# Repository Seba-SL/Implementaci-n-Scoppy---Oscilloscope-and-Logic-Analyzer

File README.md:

<h1>  Implementación Scoppy - Oscilloscope and Logic Analyzer </h1>

Fuente: https://oscilloscope.fhdm.xyz/

En este repositorio se implementa el diseño N° 5 de el proyecho Scoppy para Raspberry Pico W de microcontrolador RP2040.

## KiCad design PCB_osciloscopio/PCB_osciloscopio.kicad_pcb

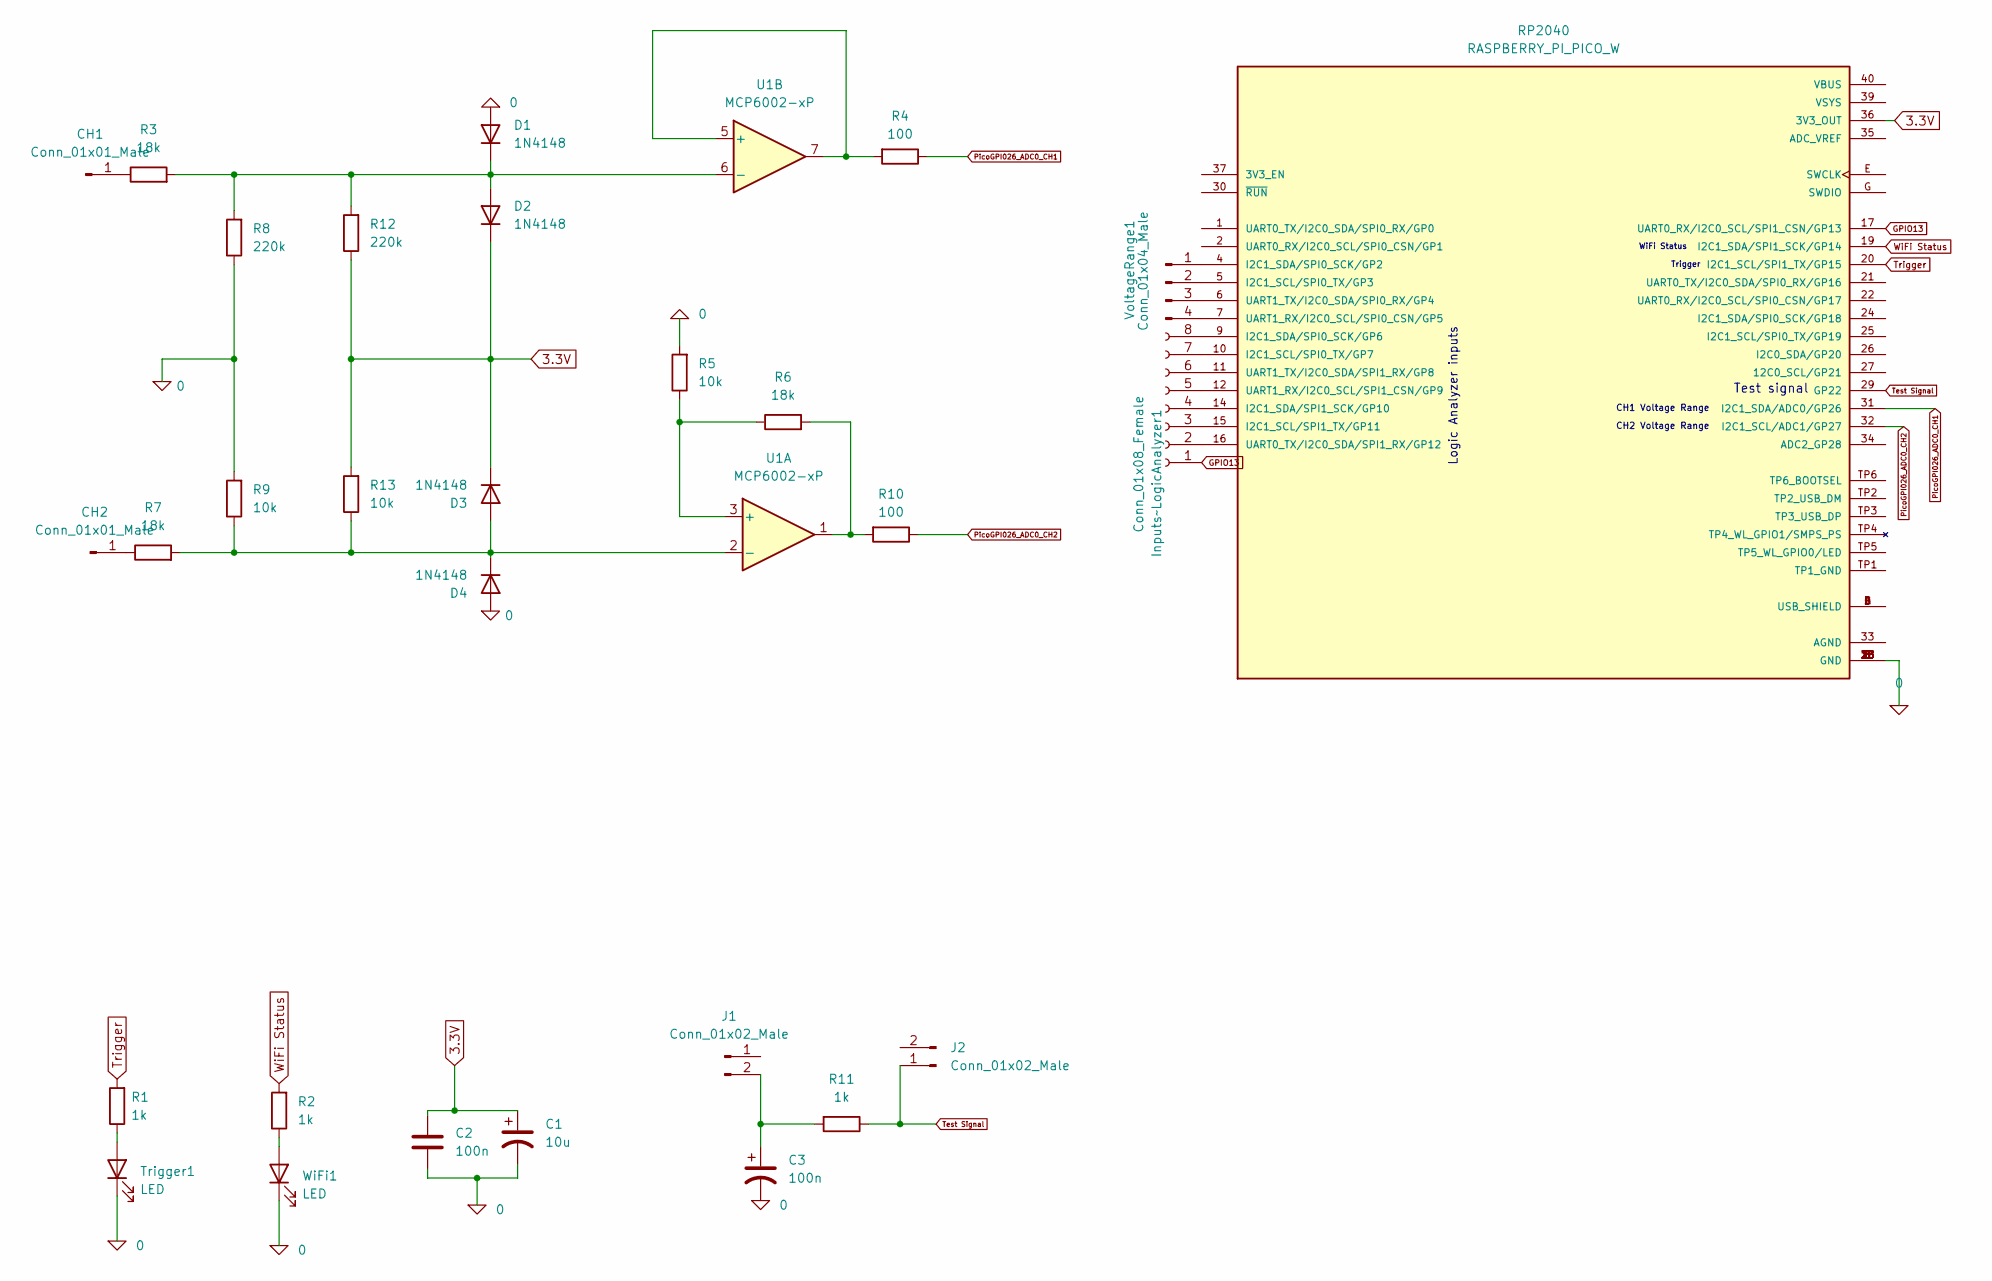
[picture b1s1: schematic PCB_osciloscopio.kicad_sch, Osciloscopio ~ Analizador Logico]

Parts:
C1: 10u; CP_Radial_D4.0mm_P1.50mm
C2: 100n; CP_Radial_D4.0mm_P1.50mm
C3: 100n; CP_Radial_D4.0mm_P2.00mm
CH1, CH2: Conn_01x01_Male; PinHeader_1x01_P1.00mm_Vertical
D1, D2, D3, D4: 1N4148; D_DO-35_SOD27_P7.62mm_Horizontal
Inputs~LogicAnalyzer1: Conn_01x08_Female; PinSocket_1x08_P2.54mm_Vertical
J1, J2: Conn_01x02_Male; PinHeader_1x02_P2.00mm_Vertical
R1, R2, R11: 1k; R_Axial_DIN0204_L3.6mm_D1.6mm_P7.62mm_Horizontal
R3, R6, R7: 18k; R_Axial_DIN0204_L3.6mm_D1.6mm_P7.62mm_Horizontal
R4, R10: 100; R_Axial_DIN0204_L3.6mm_D1.6mm_P7.62mm_Horizontal
R5, R9, R13: 10k; R_Axial_DIN0204_L3.6mm_D1.6mm_P7.62mm_Horizontal
R8, R12: 220k; R_Axial_DIN0204_L3.6mm_D1.6mm_P7.62mm_Horizontal
RP2040: RASPBERRY_PI_PICO_W; MODULE_RASPBERRY_PI_PICO_W; PARTREV 2.4
Trigger1: LED; LED_D3.0mm
U1: MCP6002-xP; DIP-8_W10.16mm_LongPads
VoltageRange1: Conn_01x04_Male; PinHeader_1x04_P2.00mm_Vertical
WiFi1: LED; LED_D3.0mm

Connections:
0: C1.2, C2.2, C3.2, D1.2 (A), D4.2 (A), R5.2, R8.1, R9.2, RP2040.3 (GND), RP2040.8 (GND), RP2040.13 (GND), RP2040.18 (GND), RP2040.23 (GND), RP2040.28 (GND), RP2040.38 (GND), RP2040.F (GND), Trigger1.1 (K), WiFi1.1 (K)
3.3V: C1.1, C2.1, D2.1 (K), D3.1 (K), R12.1, R13.2, RP2040.36 (3V3_OUT)
GPIO13: Inputs~LogicAnalyzer1.1, RP2040.17 (UART0_RX/I2C0_SCL/SPI1_CSN/GP13)
unnamed: C3.1, J1.2, R11.2
unnamed: CH1.1, R3.1
unnamed: CH2.1, R7.1
unnamed: D1.1 (K), D2.2 (A), R3.2, R8.2, R12.2, U1.6 (-)
unnamed: D3.2 (A), D4.1 (K), R7.2, R9.1, R13.1, U1.2 (-)
unnamed: Inputs~LogicAnalyzer1.2, RP2040.16 (UART0_TX/I2C0_SDA/SPI1_RX/GP12)
unnamed: Inputs~LogicAnalyzer1.3, RP2040.15 (I2C1_SCL/SPI1_TX/GP11)
unnamed: Inputs~LogicAnalyzer1.4, RP2040.14 (I2C1_SDA/SPI1_SCK/GP10)
unnamed: Inputs~LogicAnalyzer1.5, RP2040.12 (UART1_RX/I2C0_SCL/SPI1_CSN/GP9)
unnamed: Inputs~LogicAnalyzer1.6, RP2040.11 (UART1_TX/I2C0_SDA/SPI1_RX/GP8)
unnamed: Inputs~LogicAnalyzer1.7, RP2040.10 (I2C1_SCL/SPI0_TX/GP7)
unnamed: Inputs~LogicAnalyzer1.8, RP2040.9 (I2C1_SDA/SPI0_SCK/GP6)
unnamed: R1.1, Trigger1.2 (A)
unnamed: R2.1, WiFi1.2 (A)
unnamed: R4.2, U1.5 (+), U1.7
unnamed: R5.1, R6.1, U1.3 (+)
unnamed: R6.2, R10.2, U1.1
unnamed: RP2040.4 (I2C1_SDA/SPI0_SCK/GP2), VoltageRange1.1
unnamed: RP2040.5 (I2C1_SCL/SPI0_TX/GP3), VoltageRange1.2
unnamed: RP2040.6 (UART1_TX/I2C0_SDA/SPI0_RX/GP4), VoltageRange1.3
unnamed: RP2040.7 (UART1_RX/I2C0_SCL/SPI0_CSN/GP5), VoltageRange1.4
unnamed: RP2040.A (USB_SHIELD), RP2040.B (USB_SHIELD), RP2040.C (USB_SHIELD), RP2040.D (USB_SHIELD)
PicoGPI026_ADC0_CH1: R4.1, RP2040.31 (I2C1_SDA/ADC0/GP26)
PicoGPI026_ADC0_CH2: R10.1, RP2040.32 (I2C1_SCL/ADC1/GP27)
Test Signal: J2.1, R11.1, RP2040.29 (GP22)
Trigger: R1.2, RP2040.20 (I2C1_SCL/SPI1_TX/GP15)
WiFi Status: R2.2, RP2040.19 (I2C1_SDA/SPI1_SCK/GP14)

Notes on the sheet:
CH1 Voltage Range
CH2 Voltage Range
Test signal
Trigger
Logic Analyzer inputs
WiFi Status

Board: 2 copper layers, 30 parts (0 on the bottom side), 30 nets, no tracks yet.

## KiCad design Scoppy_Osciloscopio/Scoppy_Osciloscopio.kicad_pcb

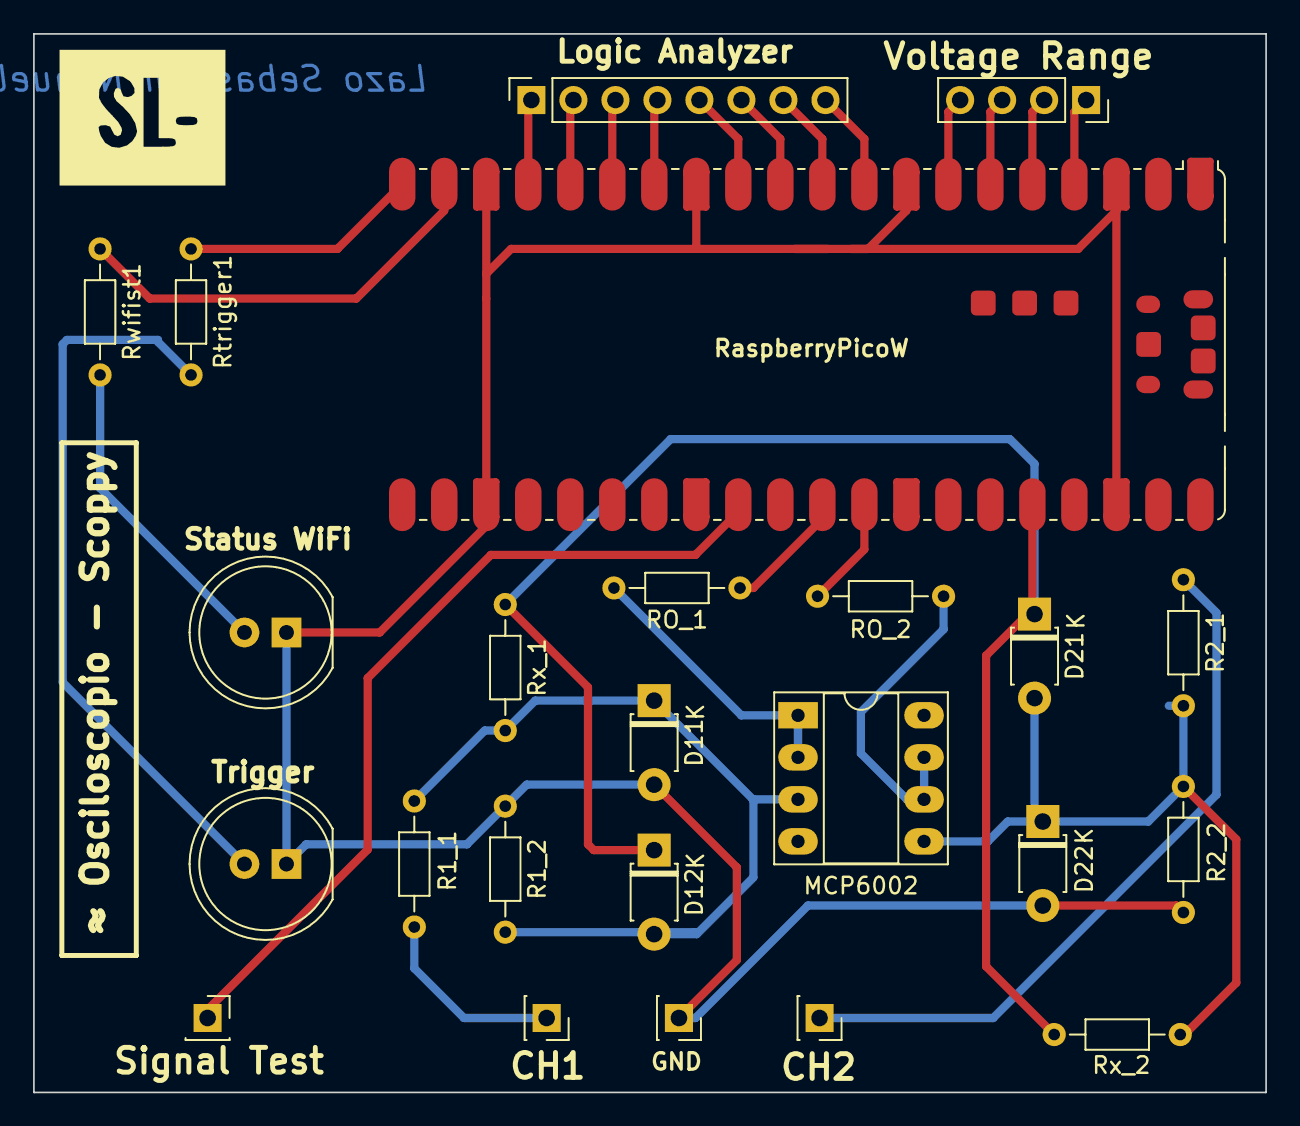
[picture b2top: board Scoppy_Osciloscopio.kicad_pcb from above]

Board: 2 copper layers, 74.5 x 64.0 mm, 24 parts (0 on the bottom side), 27 nets.

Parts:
CH1: CH1_input; PinSocket_1x01_P2.54mm_Vertical
CH2: CH2_input; PinSocket_1x01_P2.54mm_Vertical
D11, D12, D21, D22: 1N4148; D_T-1_P5.08mm_Horizontal
GND: GND; PinSocket_1x01_P2.54mm_Vertical
Logic Analyzer: LogicAnalizer; PinSocket_1x08_P2.54mm_Vertical
MCP6002: MCP6002-xP; DIP-8_W7.62mm_Socket_LongPads
R1_1, R2_1: 680k; R_Axial_DIN0204_L3.6mm_D1.6mm_P7.62mm_Horizontal
R1_2, R2_2: 330k; R_Axial_DIN0204_L3.6mm_D1.6mm_P7.62mm_Horizontal
RO_1, RO_2: 100; R_Axial_DIN0204_L3.6mm_D1.6mm_P7.62mm_Horizontal
RaspberryPicoW: RASPBERRY_PI_PICO_W; RaspberryPi_Pico_W_SMD
Rtrigger1: 1k; R_Axial_DIN0204_L3.6mm_D1.6mm_P7.62mm_Horizontal
Rwifist1: 1k; R_Axial_DIN0204_L3.6mm_D1.6mm_P7.62mm_Horizontal
Rx_1, Rx_2: 220k; R_Axial_DIN0204_L3.6mm_D1.6mm_P7.62mm_Horizontal
Signal Test: SignalTest; PinSocket_1x01_P2.54mm_Vertical
Status WiFi: LED; LED_D8.0mm
Trigger: LED; LED_D8.0mm
Voltage Range: VoltageRange; PinSocket_1x04_P2.54mm_Vertical

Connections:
0: D11.2 (A), D22.2 (A), GND.1, R1_2.1, R2_2.1, RaspberryPicoW.3 (GND), RaspberryPicoW.8 (GND), RaspberryPicoW.13 (GND), RaspberryPicoW.18 (GND), RaspberryPicoW.23 (GND), RaspberryPicoW.28 (GND), RaspberryPicoW.38 (GND), Status WiFi.1 (K), Trigger.1 (K)
3,3V: D12.1 (K), D21.1 (K), RaspberryPicoW.36 (3V3_OUT), Rx_1.1, Rx_2.1
CH1_input: CH1.1, R1_1.1
CH2_input: CH2.1, R2_1.1
GP13: Logic Analyzer.1, RaspberryPicoW.17 (UART0_RX/I2C0_SCL/SPI1_CSN/GP13)
GPIO26: RO_1.1, RaspberryPicoW.31 (I2C1_SDA/ADC0/GP26)
GPIO27: RO_2.1, RaspberryPicoW.32 (I2C1_SCL/ADC1/GP27)
unnamed: D11.1 (K), D12.2 (A), MCP6002.3 (+), R1_1.2, R1_2.2, Rx_1.2
unnamed: D21.2 (A), D22.1 (K), MCP6002.5 (+), R2_1.2, R2_2.2, Rx_2.2
unnamed: Logic Analyzer.2, RaspberryPicoW.16 (UART0_TX/I2C0_SDA/SPI1_RX/GP12)
unnamed: Logic Analyzer.3, RaspberryPicoW.15 (I2C1_SCL/SPI1_TX/GP11)
unnamed: Logic Analyzer.4, RaspberryPicoW.14 (I2C1_SDA/SPI1_SCK/GP10)
unnamed: Logic Analyzer.5, RaspberryPicoW.12 (UART1_RX/I2C0_SCL/SPI1_CSN/GP9)
unnamed: Logic Analyzer.6, RaspberryPicoW.11 (UART1_TX/I2C0_SDA/SPI1_RX/GP8)
unnamed: Logic Analyzer.7, RaspberryPicoW.10 (I2C1_SCL/SPI0_TX/GP7)
unnamed: Logic Analyzer.8, RaspberryPicoW.9 (I2C1_SDA/SPI0_SCK/GP6)
unnamed: RaspberryPicoW.5 (I2C1_SCL/SPI0_TX/GP3), Voltage Range.2
unnamed: RaspberryPicoW.4 (I2C1_SDA/SPI0_SCK/GP2), Voltage Range.1
unnamed: RaspberryPicoW.7 (UART1_RX/I2C0_SCL/SPI0_CSN/GP5), Voltage Range.4
unnamed: RaspberryPicoW.6 (UART1_TX/I2C0_SDA/SPI0_RX/GP4), Voltage Range.3
unnamed: Rwifist1.2, Status WiFi.2 (A)
unnamed: Rtrigger1.2, Trigger.2 (A)
unnamed: MCP6002.1, MCP6002.2 (-), RO_1.2
unnamed: MCP6002.6 (-), MCP6002.7, RO_2.2
Test Signal: RaspberryPicoW.29 (GP22), Signal Test.1
Trigger: RaspberryPicoW.20 (I2C1_SCL/SPI1_TX/GP15), Rtrigger1.1
WiFi-Status: RaspberryPicoW.19 (I2C1_SDA/SPI1_SCK/GP14), Rwifist1.1

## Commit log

2025-03-07 Primer Commit
